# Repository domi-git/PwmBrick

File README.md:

# PwmBrick

The aim of the project is to create a little box to control a DC-motor. The power should come from a 18650 LiIon-cell and the form-factor should be small.

**This is not a finished product! If you use anything from the project, you use it at your own risk! Be especially careful with the handling of LiIon-Batteries! If you don't know what you're doing there is always the risk of a thermal runaway which could lead to a fire or an explosion!**

## Overview

The current state of the prototype can be seen in the following picture:

**Main Features:**

| Feature                                          | Value                            |
|--------------------------------------------------|----------------------------------|
| Max. Output Current                              | 3A                               |
| Output Voltage (depends on charging status)      | 3.4V - 4.2V                      |
| PWM-States (Can be switched via the buttons)     | 4                                |
| PWM frequency                                    | 10kHz                            |
| Undervoltage Lockout (going into)                | 3.4V                             |
| Undervoltage Lockout (leaving)                   | 3.7V                             |

## Mechanics

All the CAD-Drawings were carried out with Blender. The assembly consists of the following parts:
* top-part of the housing with cutouts for the buttons, the charging port and the LEDs
* bottom-part of the housing
* fibre-optics to guide the LED light
* plus- and minus-button
* pcb with soldered battery-holder for 18650-cell

You can see the listed parts in the following picture:

## Electronics

The schematic and the layout was done in KiCad. The goal was to keep the overall space of the electronics very close to the footprint of the battery-holder for the 18650 LiIon cell. 

**Block diagram**

**Schematic**

**Layout**

## Software

TBD

## Possible improvements

### Documentation
* Snap-Fit Design
* The states of the PWM
* Debugging capabilities with TermControl
* How to flash new software

### Mechanics

* Incoporate a cutout for the micro-usb charging port. At the moment the cable does not fit.

### Electronics

For the current PCB:
* Accurately measure the undervoltage lockout thresholds
* Measure the charging current over time

For next PCB revision:
* Incorporate a way to use the charging LED from the microcontroller (It should not be exclusive to the charging IC)
* Low-pass for the measurement of the battery-voltage
* Pull-Downs/Pull-Ups for the Uart/Flash connector

### Software   

* Clean up the code
* Implement a soft transition of the pwm duty-cycle in state changes
* Replace as much of generated code from the IDE with own implementations

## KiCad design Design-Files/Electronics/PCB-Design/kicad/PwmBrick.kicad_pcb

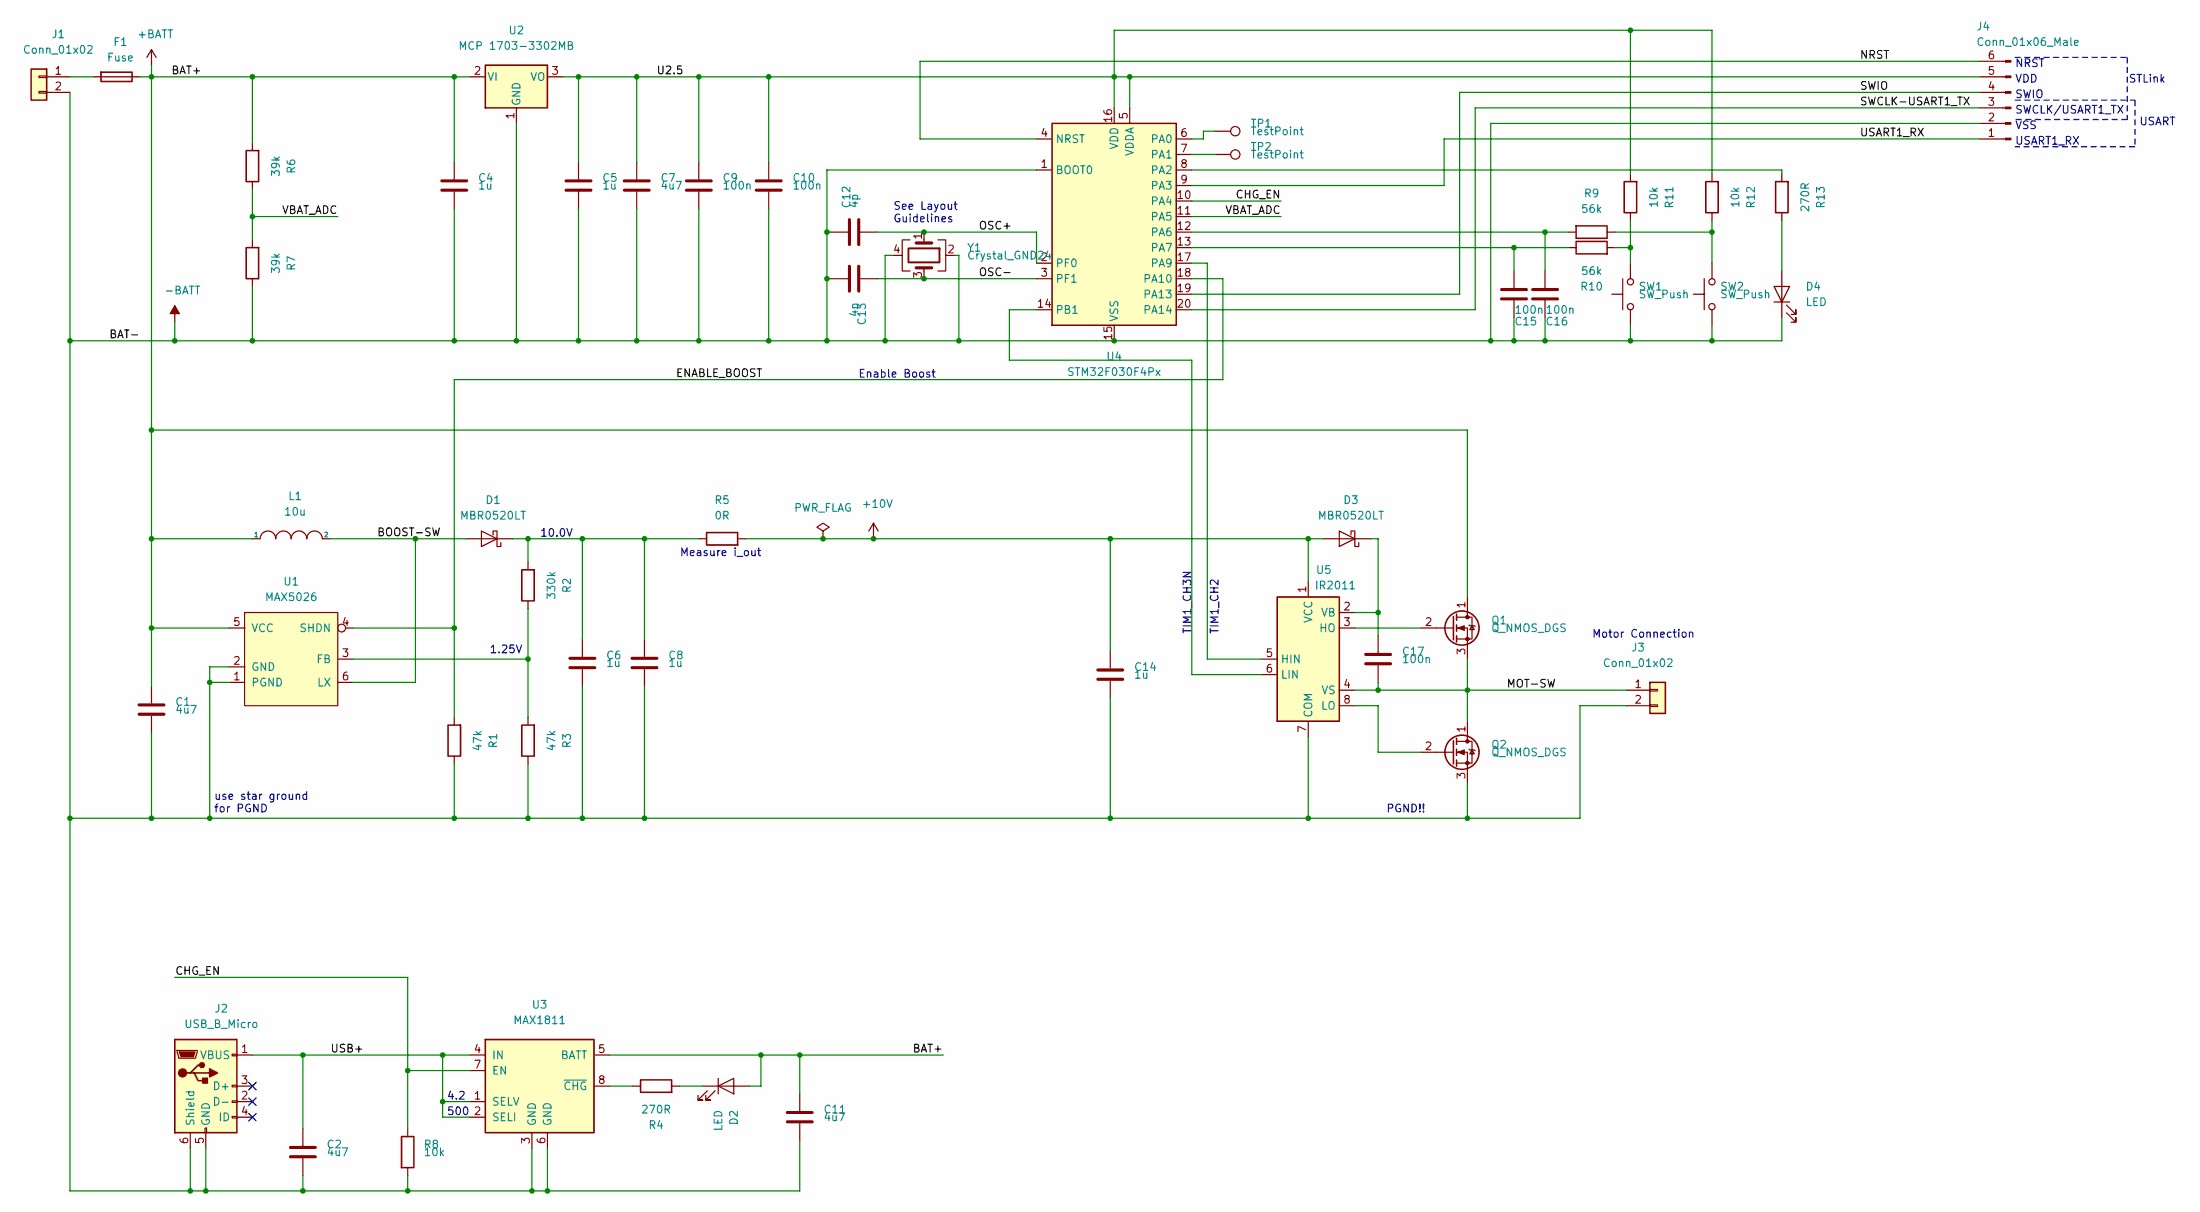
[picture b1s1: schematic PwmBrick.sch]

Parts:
C1, C2, C7, C11: 4u7; C_0603_1608Metric_Pad1.05x0.95mm_HandSolder
C4, C5, C6, C8, C14: 1u; C_0603_1608Metric_Pad1.05x0.95mm_HandSolder
C9, C10, C15, C16, C17: 100n; C_0603_1608Metric_Pad1.05x0.95mm_HandSolder
C12, C13: 4p; C_0603_1608Metric_Pad1.05x0.95mm_HandSolder
D1, D3: MBR0520LT; D_SOD-123
D2, D4: LED; LED_PLCC-2
F1: Fuse; Fuse_2512_6332Metric
J1: Conn_01x02; battery_holder_18650
J2: USB_B_Micro; USB_Micro-B_Wuerth_629105150521
J3: Conn_01x02; Motor_Connector
J4: Conn_01x06_Male; PinHeader_1x06_P1.27mm_Horizontal
L1: 10u; L_6.3x6.3_H3
Q1, Q2: Q_NMOS_DGS; SOIC-8-SI4114DY-GE3
R1, R3: 47k; R_0805_2012Metric_Pad1.15x1.40mm_HandSolder
R2: 330k; R_0805_2012Metric_Pad1.15x1.40mm_HandSolder
R4, R13: 270R; R_0805_2012Metric_Pad1.15x1.40mm_HandSolder
R5: 0R; R_0805_2012Metric_Pad1.15x1.40mm_HandSolder
R6, R7: 39k; R_0805_2012Metric_Pad1.15x1.40mm_HandSolder
R8, R11, R12: 10k; R_0805_2012Metric_Pad1.15x1.40mm_HandSolder
R9, R10: 56k; R_0805_2012Metric_Pad1.15x1.40mm_HandSolder
SW1, SW2: SW_Push; SW_Push_1P1T_NO_6x6mm_H9.5mm
TP1, TP2: TestPoint; TestPoint_Pad_1.0x1.0mm
U1: MAX5026; TSOT-23-6
U2: MCP 1703-3302MB; SOT-89-3
U3: MAX1811; SOIC-8_3.9x4.9mm_P1.27mm
U4: STM32F030F4Px; TSSOP-20_4.4x6.5mm_P0.65mm
U5: IR2011; SO-8_3.9x4.9mm_P1.27mm
Y1: Crystal_GND24; Crystal_SMD_EuroQuartz_MQ-4Pin_7.0x5.0mm

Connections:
+10V: C14.1, D3.2 (A), R5.2, U5.1 (VCC)
+BATT: C1.1, C4.1, C11.1, D2.2 (A), F1.1, L1.1, Q1.1 (D), R6.2, U1.5 (VCC), U2.2 (VI), U3.5 (BATT)
-BATT: C1.2, C2.2, C4.2, C5.2, C6.2, C7.2, C8.2, C9.2, C10.2, C11.2, C12.1, C13.2, C14.2, C15.2, C16.2, D4.1 (K), J1.2, J2.5 (GND), J2.6 (Shield), J3.2, J4.2, Q2.3 (S), R1.1, R3.1, R7.1, R8.2, SW1.1, SW2.1, U1.1 (PGND), U1.2 (GND), U2.1 (GND), U3.3 (GND), U3.6 (GND), U4.1 (BOOT0), U4.15 (VSS), U5.7 (COM), Y1.2, Y1.4
/BOOST-SW: D1.2 (A), L1.2, U1.6 (LX)
/CHG_EN: R8.1, U3.7 (EN), U4.10 (PA4)
/ENABLE_BOOST: R1.2, U1.4 (SHDN), U4.18 (PA10)
/MOT-SW: C17.2, J3.1, Q1.3 (S), Q2.1 (D), U5.4 (VS)
/NRST: J4.6, U4.4 (NRST)
/OSC+: C12.2, U4.2 (PF0), Y1.1
/OSC-: C13.1, U4.3 (PF1), Y1.3
/SWCLK-USART1_TX: J4.3, U4.20 (PA14)
/SWIO: J4.4, U4.19 (PA13)
/U2.5: C5.1, C7.1, C9.1, C10.1, J4.5, R11.2, R12.2, U2.3 (VO), U4.5 (VDDA), U4.16 (VDD)
/USART1_RX: J4.1, U4.9 (PA3)
/USB+: C2.1, J2.1 (VBUS), U3.1 (SELV), U3.2 (SELI), U3.4 (IN)
/VBAT_ADC: R6.1, R7.2, U4.11 (PA5)
unnamed: C6.1, C8.1, D1.1 (K), R2.2, R5.1
unnamed: C15.1, R10.1, U4.13 (PA7)
unnamed: C16.1, R9.2, U4.12 (PA6)
unnamed: C17.1, D3.1 (K), U5.2 (VB)
unnamed: D2.1 (K), R4.2
unnamed: D4.2 (A), R13.1
unnamed: F1.2, J1.1
unnamed: Q1.2 (G), U5.3 (HO)
unnamed: Q2.2 (G), U5.8 (LO)
unnamed: R2.1, R3.2, U1.3 (FB)
unnamed: R4.1, U3.8 (~CHG)
unnamed: R10.2, R11.1, SW1.2
unnamed: R9.1, R12.1, SW2.2
unnamed: R13.2, U4.8 (PA2)
unnamed: TP1.1, U4.6 (PA0)
unnamed: TP2.1, U4.7 (PA1)
unnamed: U4.14 (PB1), U5.6 (LIN)
unnamed: U4.17 (PA9), U5.5 (HIN)

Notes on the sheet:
Motor Connection
See Layout Guidelines
1.25V
use star ground for PGND
10.0V
Measure i_out
Enable Boost
PGND!!
TIM1_CH3N
TIM1_CH2
USART1_RX
VSS
VDD
SWIO
NRST
STLink
500
4.2
SWCLK/USART1_TX
USART

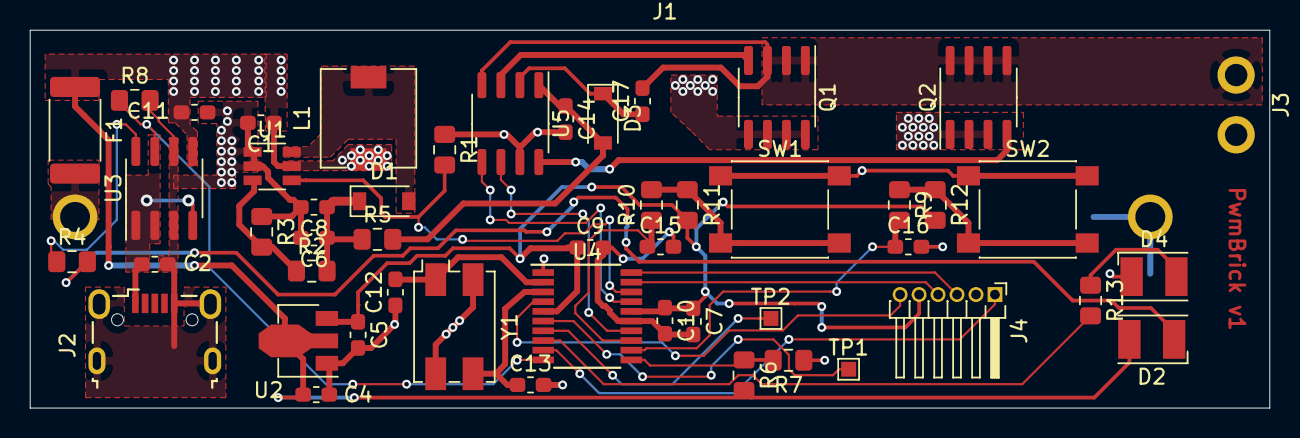
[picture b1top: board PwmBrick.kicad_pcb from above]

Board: 2 copper layers, 83.0 x 25.3 mm, 51 parts (0 on the bottom side), 34 nets.

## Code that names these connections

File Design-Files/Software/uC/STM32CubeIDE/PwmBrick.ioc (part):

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Mcu.Name=STM32F030F4Px
Mcu.Package=TSSOP20
Mcu.UserName=STM32F030F4Px
PA10.GPIOParameters=GPIO_Label
PA10.GPIO_Label=Start_10V
PA10.Signal=GPIO_Output
PA2.GPIOParameters=GPIO_Label
PA2.GPIO_Label=LED_Green
PA2.Signal=GPIO_Output
PA3.Signal=USART1_RX
PA4.GPIOParameters=GPIO_Label
PA4.GPIO_Label=Charge_Enable
PA4.Signal=GPIO_Output
PA5.Mode=IN5
PA5.Signal=ADC_IN5
PA6.GPIOParameters=GPIO_Label
PA6.GPIO_Label=Switch_Plus
PA6.Signal=GPIO_Input
PA7.GPIOParameters=GPIO_Label
PA7.GPIO_Label=Switch_Minus
PA7.Signal=GPIO_Input
PA9.GPIOParameters=GPIO_Label
PA9.GPIO_Label=Pwm_Mos_High
PA9.Signal=S_TIM1_CH2
PB1.GPIOParameters=GPIO_Label
PB1.GPIO_Label=Pwm_Mos_Low
PB1.Mode=PWM Generation3 CH3N
PB1.Signal=TIM1_CH3N
PF0-OSC_IN.Mode=HSE-External-Oscillator
PF0-OSC_IN.Signal=RCC_OSC_IN
PF1-OSC_OUT.Mode=HSE-External-Oscillator
PF1-OSC_OUT.Signal=RCC_OSC_OUT
RCC.SYSCLKFreq_VALUE=32000000
RCC.SYSCLKSource=RCC_SYSCLKSOURCE_PLLCLK
board=custom

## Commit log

2020-11-29 Changed the LDO for the microcontroller from the old 2.5V to the new 3.3V
2020-11-29 Added first documentation of the mechanics.
2020-11-29 Changing Mechanics Image
2020-11-29 Added new content to readme
2020-11-29 Expanded Readme
2020-11-29 Improvements for the Readme
2020-11-29 - Added a dummy Cable to the mechanics-CAD to show the connection to the motor - Changed the Readme
2020-11-29 Readme...
2020-11-29 Readme Readme Readme
2020-11-29 Readme again
2020-12-01 Added explosion-drawing to mechanics-CAD and the readme
2020-12-04 Started with Block Diagram Added Schematic to the Readme
2020-12-04 Layout of Readme
2020-12-06 Create first useful version of the block diagram Added the block diagram to the readme
2020-12-06 Small modification to readme
2021-02-07 Mechanical Improvements: - Made the micro-usb cutout larger to fit the connector - Made the diameter for the fibre-optics cutouts for the LEDs larger
